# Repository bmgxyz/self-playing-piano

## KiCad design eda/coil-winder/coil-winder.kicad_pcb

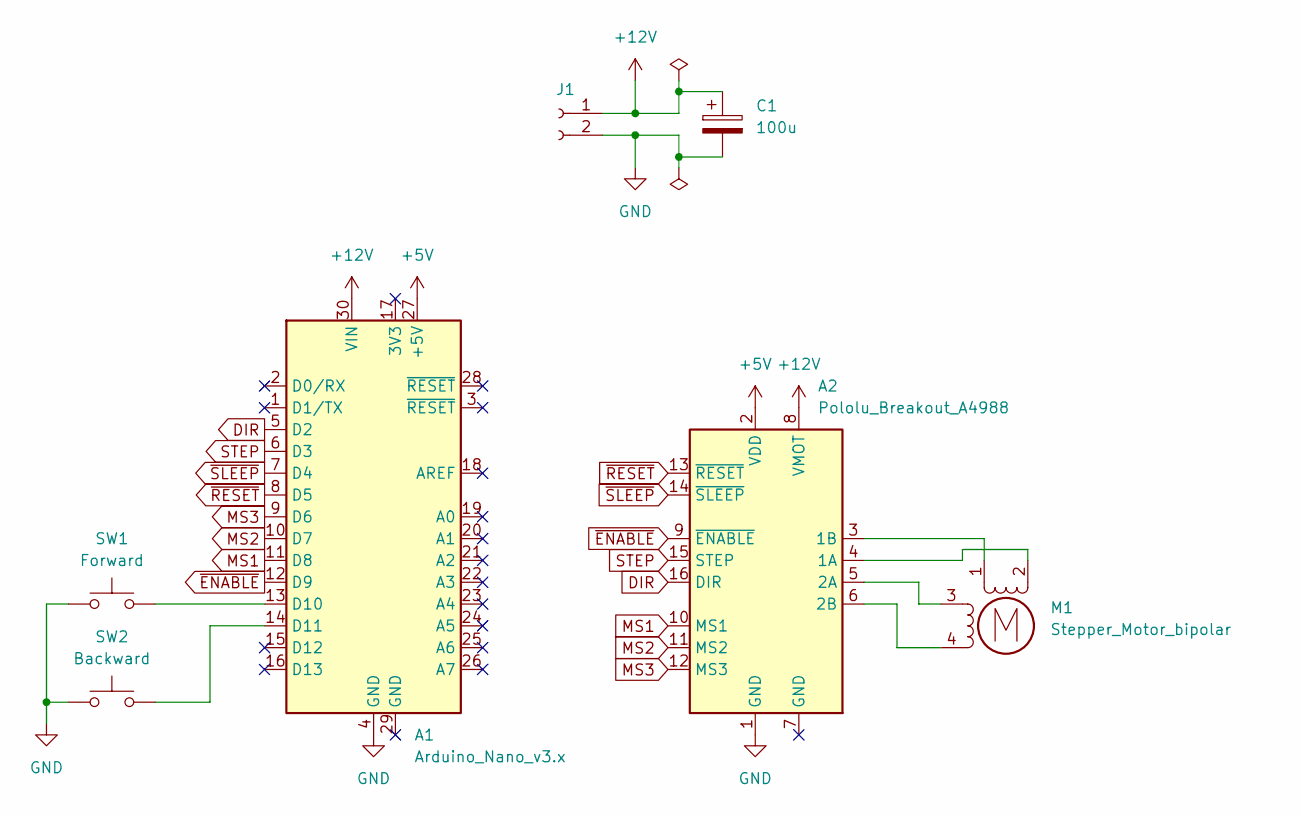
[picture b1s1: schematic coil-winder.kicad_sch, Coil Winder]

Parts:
A1: Arduino_Nano_v3.x; Arduino_Nano
A2: Pololu_Breakout_A4988; Pololu_Breakout-16_15.2x20.3mm
C1: 100u; CP_Radial_D5.0mm_P2.50mm
J1: Conn_01x02_Socket; JST_EH_B2B-EH-A_1x02_P2.50mm_Vertical
M1: Stepper_Motor_bipolar; JST_EH_B2B-EH-A_1x02_P2.50mm_Vertical_Double
SW1: Forward; SW_PUSH_6mm
SW2: Backward; SW_PUSH_6mm

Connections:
+5V: A1.27 (+5V), A2.2 (VDD)
+12V: A1.30 (VIN), A2.8 (VMOT), C1.1, J1.1
DIR: A1.5 (D2), A2.16 (DIR)
GND: A1.4 (GND), A2.1 (GND), C1.2, J1.2, SW1.1, SW2.1
MS1: A1.11 (D8), A2.10 (MS1)
MS2: A1.10 (D7), A2.11 (MS2)
MS3: A1.9 (D6), A2.12 (MS3)
unnamed: A1.13 (D10), SW1.2
unnamed: A1.14 (D11), SW2.2
unnamed: A2.4 (1A), M1.2 (-)
unnamed: A2.3 (1B), M1.1
unnamed: A2.5 (2A), M1.3
unnamed: A2.6 (2B), M1.4
STEP: A1.6 (D3), A2.15 (STEP)
~ENABLE: A1.12 (D9), A2.9 (~ENABLE)
~RESET: A1.8 (D5), A2.13 (~RESET)
~SLEEP: A1.7 (D4), A2.14 (~SLEEP)

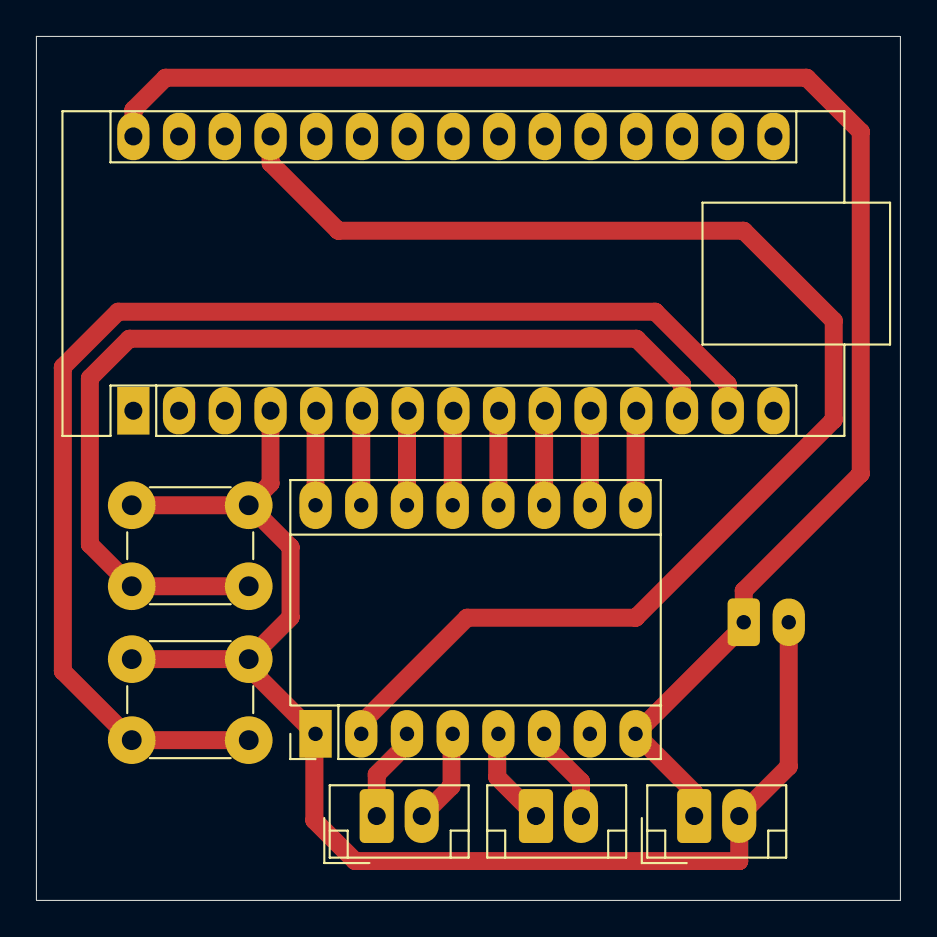
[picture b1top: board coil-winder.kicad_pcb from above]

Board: 2 copper layers, 48.0 x 48.0 mm, 7 parts (0 on the bottom side), 17 nets.

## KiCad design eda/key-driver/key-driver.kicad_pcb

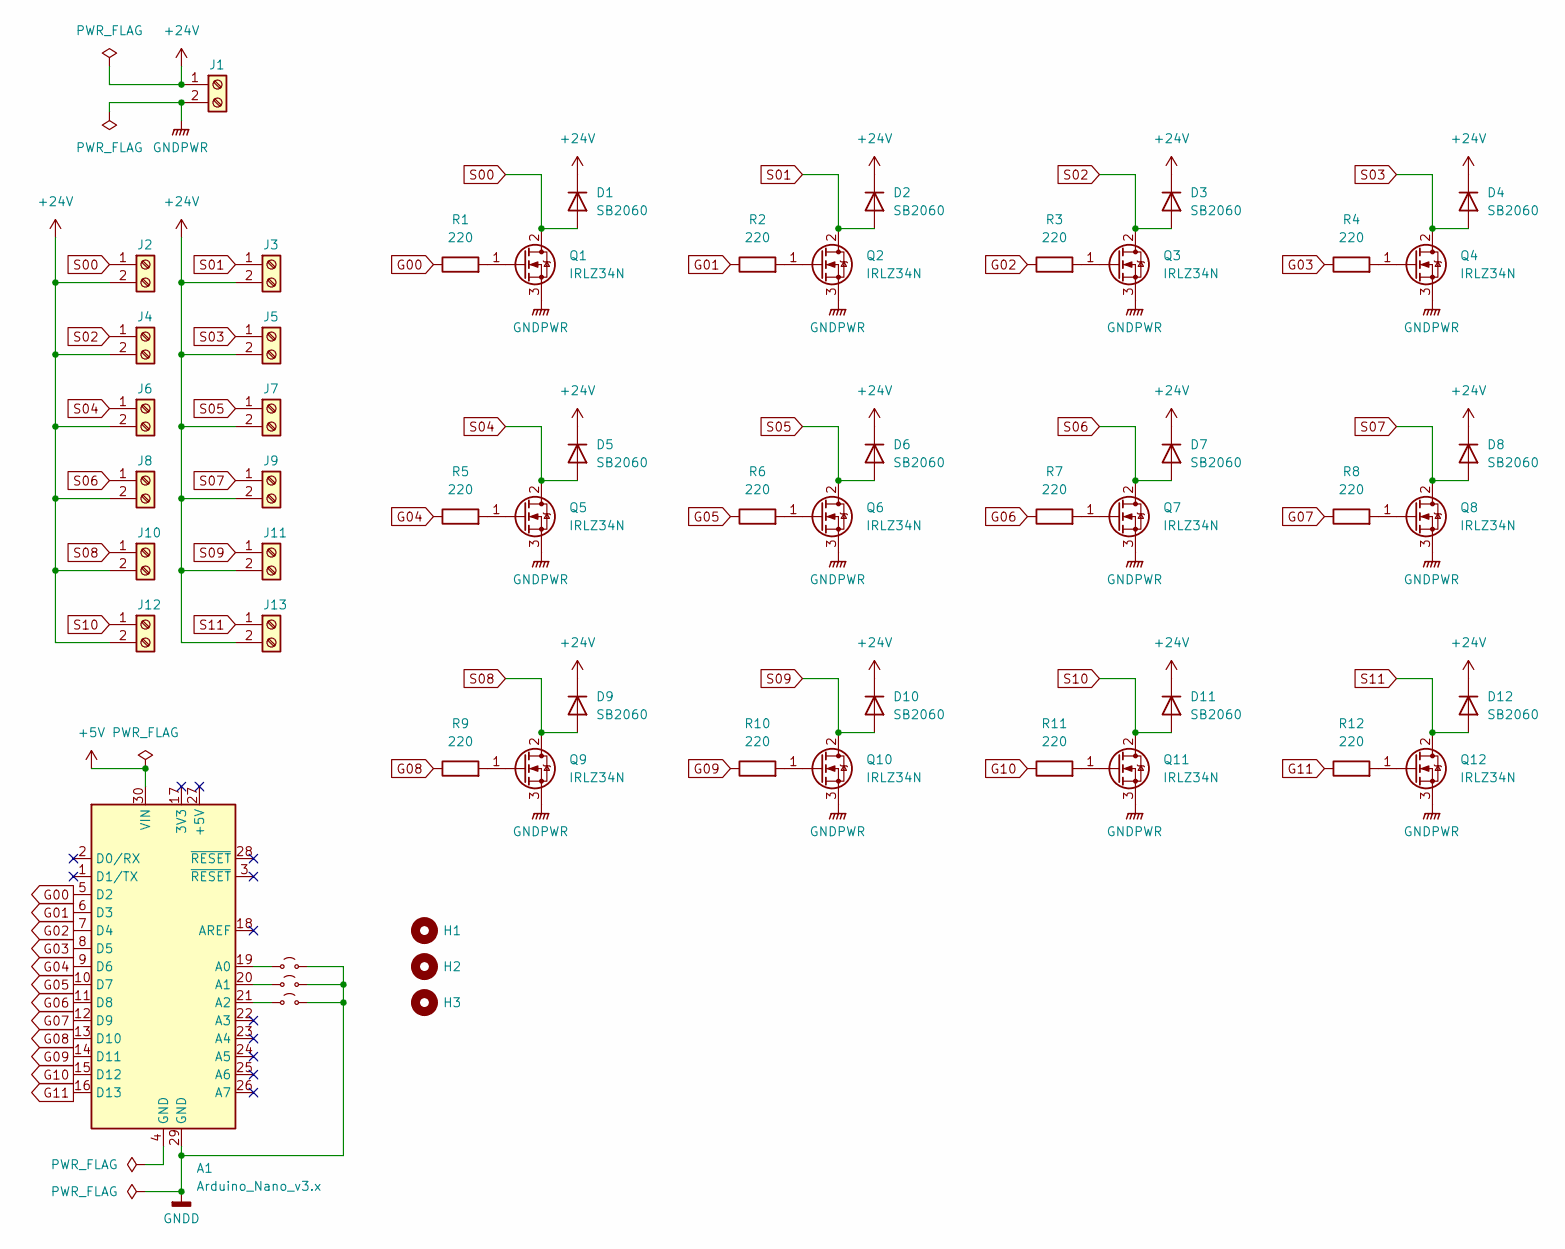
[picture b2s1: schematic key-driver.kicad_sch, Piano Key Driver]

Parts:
A1: Arduino_Nano_v3.x; Arduino_Nano
D1, D2, D3, D4, D5, D6, D7, D8, D9, D10, D11, D12: SB2060; D_DO-201AE_P5.08mm_Vertical_KathodeUp
H1, H2, H3: MountingHole; MountingHole_3.2mm_M3
J1, J2, J3, J4, J5, J6, J7, J8, J9, J10, J11, J12, J13: Screw_Terminal_01x02; JST_EH_B2B-EH-A_1x02_P2.50mm_Vertical
JP1, JP2, JP3: Jumper_2_Small_Open; PinHeader_1x02_P2.54mm_Vertical
Q1, Q2, Q3, Q4, Q5, Q6, Q7, Q8, Q9, Q10, Q11, Q12: IRLZ34N; TO-220-3_Vertical
R1, R2, R3, R4, R5, R6, R7, R8, R9, R10, R11, R12: 220; R_Axial_DIN0204_L3.6mm_D1.6mm_P7.62mm_Horizontal

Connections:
+5V: A1.30 (VIN)
+24V: D1.1 (K), D2.1 (K), D3.1 (K), D4.1 (K), D5.1 (K), D6.1 (K), D7.1 (K), D8.1 (K), D9.1 (K), D10.1 (K), D11.1 (K), D12.1 (K), J1.1, J2.2, J3.2, J4.2, J5.2, J6.2, J7.2, J8.2, J9.2, J10.2, J11.2, J12.2, J13.2
G00: A1.5 (D2), R1.1
G01: A1.6 (D3), R2.1
G02: A1.7 (D4), R3.1
G03: A1.8 (D5), R4.1
G04: A1.9 (D6), R5.1
G05: A1.10 (D7), R6.1
G06: A1.11 (D8), R7.1
G07: A1.12 (D9), R8.1
G08: A1.13 (D10), R9.1
G09: A1.14 (D11), R10.1
G10: A1.15 (D12), R11.1
G11: A1.16 (D13), R12.1
GNDD: A1.29 (GND), JP1.2 (B), JP2.2 (B), JP3.2 (B)
GNDPWR: J1.2, Q1.3 (S), Q2.3 (S), Q3.3 (S), Q4.3 (S), Q5.3 (S), Q6.3 (S), Q7.3 (S), Q8.3 (S), Q9.3 (S), Q10.3 (S), Q11.3 (S), Q12.3 (S)
unnamed: A1.19 (A0), JP1.1 (A)
unnamed: A1.20 (A1), JP2.1 (A)
unnamed: A1.21 (A2), JP3.1 (A)
unnamed: Q1.1 (G), R1.2
unnamed: Q2.1 (G), R2.2
unnamed: Q3.1 (G), R3.2
unnamed: Q4.1 (G), R4.2
unnamed: Q5.1 (G), R5.2
unnamed: Q6.1 (G), R6.2
unnamed: Q7.1 (G), R7.2
unnamed: Q8.1 (G), R8.2
unnamed: Q9.1 (G), R9.2
unnamed: Q10.1 (G), R10.2
unnamed: Q11.1 (G), R11.2
unnamed: Q12.1 (G), R12.2
S00: D1.2 (A), J2.1, Q1.2 (D)
S01: D2.2 (A), J3.1, Q2.2 (D)
S02: D3.2 (A), J4.1, Q3.2 (D)
S03: D4.2 (A), J5.1, Q4.2 (D)
S04: D5.2 (A), J6.1, Q5.2 (D)
S05: D6.2 (A), J7.1, Q6.2 (D)
S06: D7.2 (A), J8.1, Q7.2 (D)
S07: D8.2 (A), J9.1, Q8.2 (D)
S08: D9.2 (A), J10.1, Q9.2 (D)
S09: D10.2 (A), J11.1, Q10.2 (D)
S10: D11.2 (A), J12.1, Q11.2 (D)
S11: D12.2 (A), J13.1, Q12.2 (D)

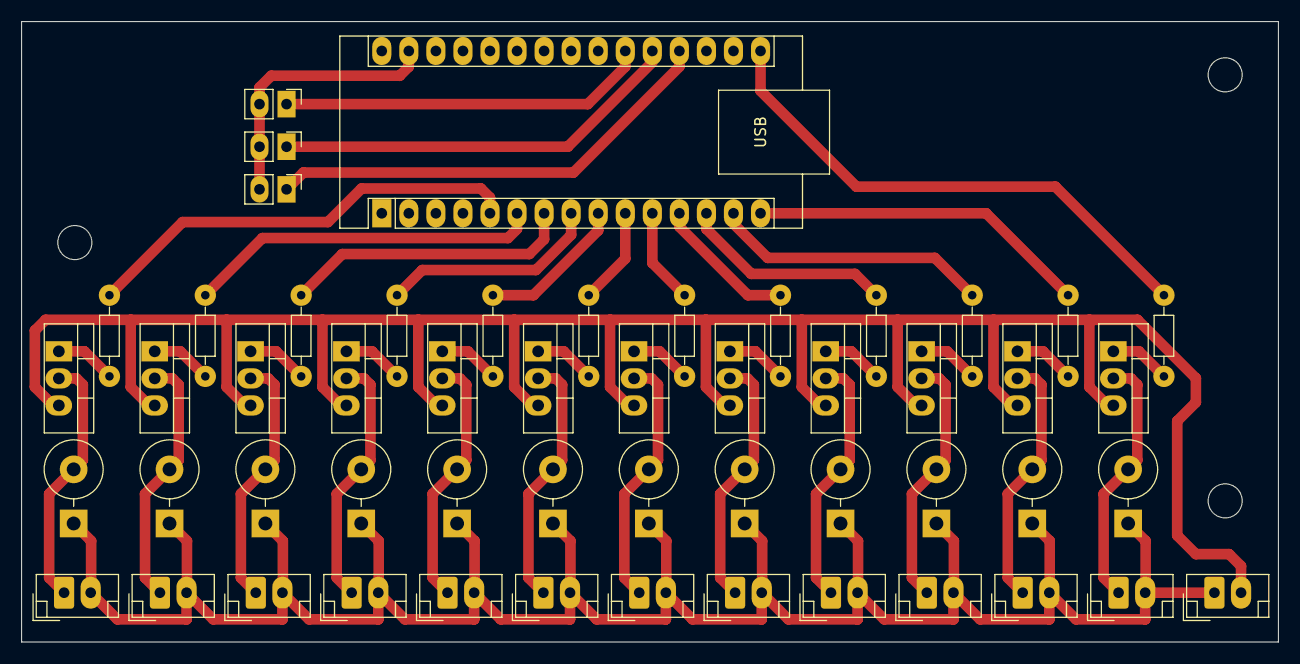
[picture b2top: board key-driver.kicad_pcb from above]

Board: 2 copper layers, 118.0 x 58.2 mm, 56 parts (0 on the bottom side), 42 nets.

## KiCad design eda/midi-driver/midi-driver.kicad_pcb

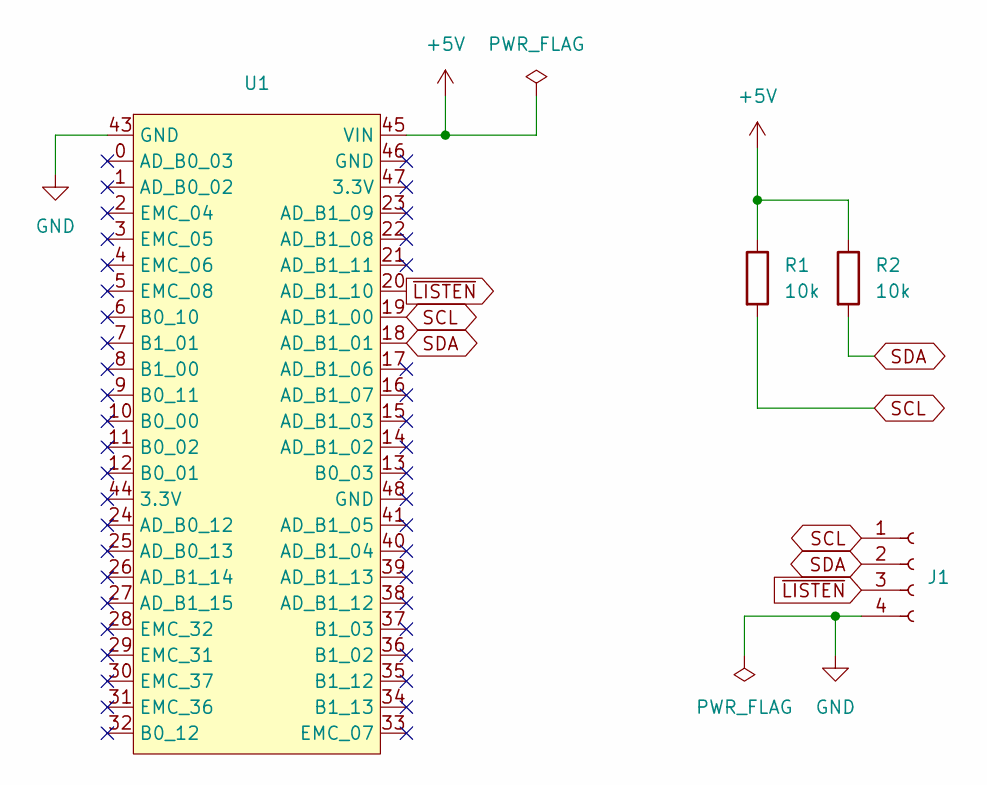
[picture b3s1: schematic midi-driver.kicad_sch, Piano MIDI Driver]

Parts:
J1: Conn_01x04_Socket; PinSocket_1x04_P2.54mm_Vertical
R1, R2: 10k; R_Axial_DIN0204_L3.6mm_D1.6mm_P7.62mm_Horizontal
U1: Teensy41

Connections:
+5V: R1.1, R2.1, U1.45 (VIN)
GND: J1.4, U1.43 (GND)
SCL: J1.1, R1.2, U1.19 (AD_B1_00)
SDA: J1.2, R2.2, U1.18 (AD_B1_01)
~LISTEN: J1.3, U1.20 (AD_B1_10)

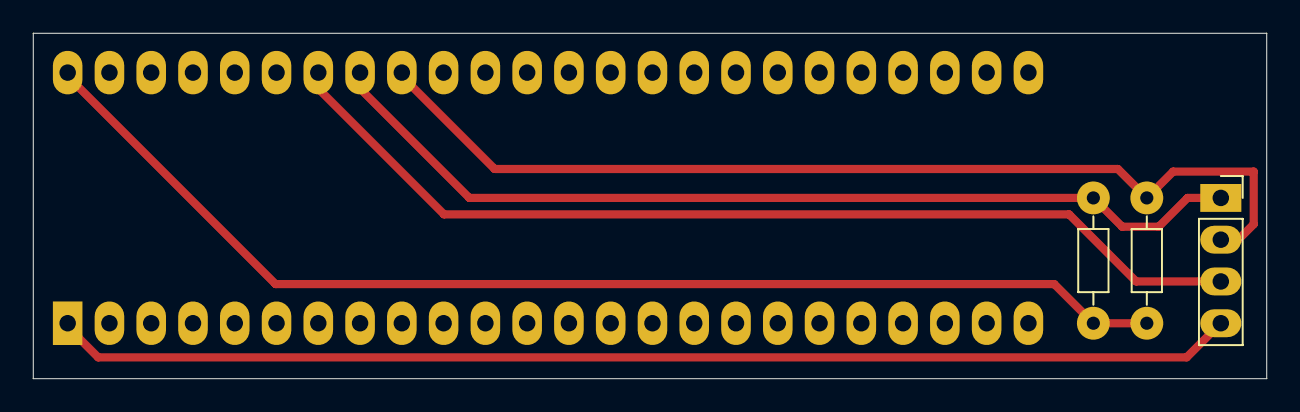
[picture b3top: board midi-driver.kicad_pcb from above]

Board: 2 copper layers, 75.0 x 21.0 mm, 4 parts (0 on the bottom side), 5 nets.

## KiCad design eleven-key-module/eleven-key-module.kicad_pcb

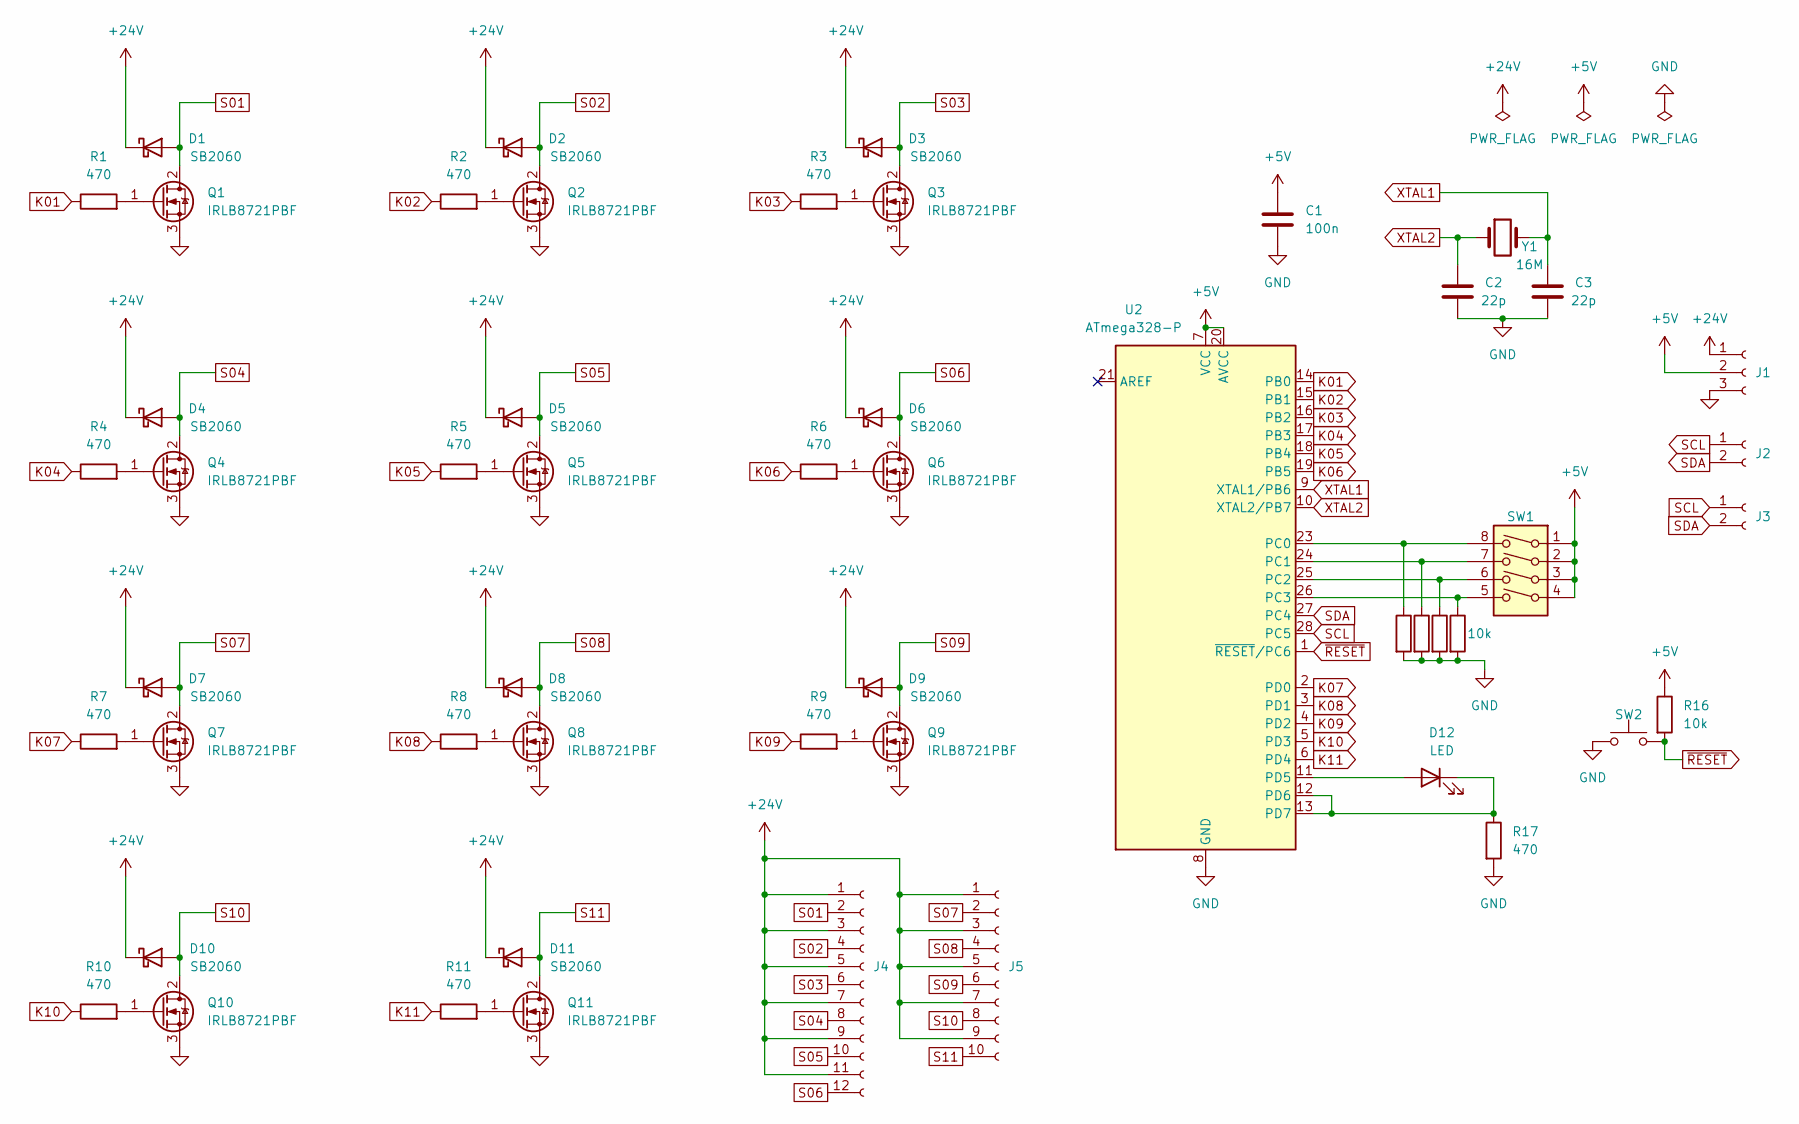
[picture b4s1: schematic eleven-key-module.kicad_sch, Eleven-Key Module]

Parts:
C1: 100n; C_Rect_L4.6mm_W3.8mm_P2.50mm_MKS02_FKP02
C2, C3: 22p; C_Rect_L4.0mm_W2.5mm_P2.50mm
D1, D2, D3, D4, D5, D6, D7, D8, D9, D10, D11: SB2060; D_DO-201AD_P15.24mm_Horizontal
D12: LED; LED_D5.0mm
J1: Conn_01x03_Socket; TerminalBlock_Xinya_XY308-2.54-3P_1x03_P2.54mm_Horizontal
J2, J3: Conn_01x02_Female; PinHeader_1x02_P2.54mm_Vertical
J4: Conn_01x12_Socket; TerminalBlock_Xinya_XY308-2.54-12P_1x12_P2.54mm_Horizontal
J5: Conn_01x10_Socket; TerminalBlock_Xinya_XY308-2.54-10P_1x10_P2.54mm_Horizontal
Q1, Q2, Q3, Q4, Q5, Q6, Q7, Q8, Q9, Q10, Q11: IRLB8721PBF; TO-220-3_Vertical
R1, R2, R3, R4, R5, R6, R7, R8, R9, R10, R11, R17: 470; R_Axial_DIN0204_L3.6mm_D1.6mm_P7.62mm_Horizontal
R12, R13, R14, R15, R16: 10k; R_Axial_DIN0204_L3.6mm_D1.6mm_P7.62mm_Horizontal
SW1: SW_DIP_x04; DIP-8_W7.62mm
SW2: SW_Push; SW_PUSH_6mm
U2: ATmega328-P; DIP-28_W7.62mm
Y1: 16M; Crystal_HC49-U_Vertical

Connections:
+5V: C1.1, J1.2, R16.1, SW1.1, SW1.2, SW1.3, SW1.4, U2.7 (VCC), U2.20 (AVCC)
+24V: D1.1 (K), D2.1 (K), D3.1 (K), D4.1 (K), D5.1 (K), D6.1 (K), D7.1 (K), D8.1 (K), D9.1 (K), D10.1 (K), D11.1 (K), J1.1, J4.1, J4.3, J4.5, J4.7, J4.9, J4.11, J5.1, J5.3, J5.5, J5.7, J5.9
GND: C1.2, C2.1, C3.1, J1.3, Q1.3 (S), Q2.3 (S), Q3.3 (S), Q4.3 (S), Q5.3 (S), Q6.3 (S), Q7.3 (S), Q8.3 (S), Q9.3 (S), Q10.3 (S), Q11.3 (S), R12.2, R13.2, R14.2, R15.2, R17.2, SW2.1, U2.8 (GND), U2.22 (GND)
K01: R1.1, U2.14 (PB0)
K02: R2.1, U2.15 (PB1)
K03: R3.1, U2.16 (PB2)
K04: R4.1, U2.17 (PB3)
K05: R5.1, U2.18 (PB4)
K06: R6.1, U2.19 (PB5)
K07: R7.1, U2.2 (PD0)
K08: R8.1, U2.3 (PD1)
K09: R9.1, U2.4 (PD2)
K10: R10.1, U2.5 (PD3)
K11: R11.1, U2.6 (PD4)
unnamed: D12.2 (A), U2.11 (PD5)
unnamed: D12.1 (K), R17.1, U2.12 (PD6), U2.13 (PD7)
unnamed: Q1.1 (G), R1.2
unnamed: Q2.1 (G), R2.2
unnamed: Q3.1 (G), R3.2
unnamed: Q4.1 (G), R4.2
unnamed: Q5.1 (G), R5.2
unnamed: Q6.1 (G), R6.2
unnamed: Q7.1 (G), R7.2
unnamed: Q8.1 (G), R8.2
unnamed: Q9.1 (G), R9.2
unnamed: Q10.1 (G), R10.2
unnamed: Q11.1 (G), R11.2
unnamed: R12.1, SW1.8, U2.23 (PC0)
unnamed: R13.1, SW1.7, U2.24 (PC1)
unnamed: R14.1, SW1.6, U2.25 (PC2)
unnamed: R15.1, SW1.5, U2.26 (PC3)
S01: D1.2 (A), J4.2, Q1.2 (D)
S02: D2.2 (A), J4.4, Q2.2 (D)
S03: D3.2 (A), J4.6, Q3.2 (D)
S04: D4.2 (A), J4.8, Q4.2 (D)
S05: D5.2 (A), J4.10, Q5.2 (D)
S06: D6.2 (A), J4.12, Q6.2 (D)
S07: D7.2 (A), J5.2, Q7.2 (D)
S08: D8.2 (A), J5.4, Q8.2 (D)
S09: D9.2 (A), J5.6, Q9.2 (D)
S10: D10.2 (A), J5.8, Q10.2 (D)
S11: D11.2 (A), J5.10, Q11.2 (D)
SCL: J2.1, J3.1, U2.28 (PC5)
SDA: J2.2, J3.2, U2.27 (PC4)
XTAL1: C3.2, U2.9 (XTAL1/PB6), Y1.2
XTAL2: C2.2, U2.10 (XTAL2/PB7), Y1.1
~RESET: R16.2, SW2.2, U2.1 (~RESET/PC6)

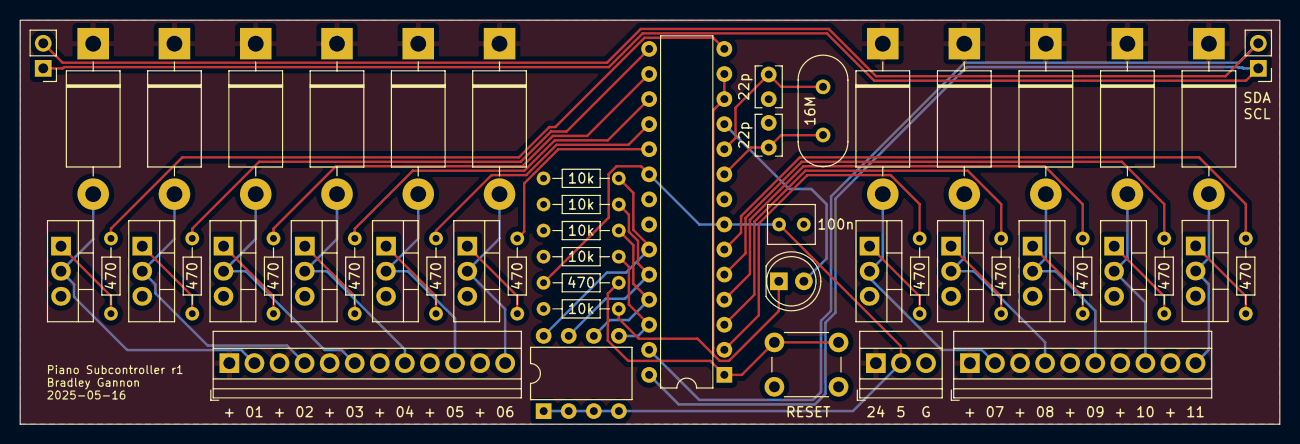
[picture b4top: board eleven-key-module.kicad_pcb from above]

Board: 2 copper layers, 127.6 x 40.9 mm, 52 parts (0 on the bottom side), 47 nets.

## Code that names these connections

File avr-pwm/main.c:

#include <avr/io.h>
#include <avr/interrupt.h>
#include <stdbool.h>

#define TWI_ACK_NEXT  { TWCR = (1 << TWINT) | (1 << TWEN) | (1 << TWEA) | (1 << TWIE); }
#define TWI_NACK_NEXT { TWCR = (1 << TWINT) | (1 << TWEN) | (1 << TWIE); }

extern void pwm(uint8_t *table_b, uint8_t *table_d);

// libc zeros these arrays automatically
static uint8_t table_b[127];
static uint8_t table_d[127];

enum state {
    idle, first, second, third
};

static volatile enum state s = idle;
static volatile uint16_t message = 0;
static volatile uint8_t key_idx = 0;
static volatile uint8_t key_vel = 0;

const uint8_t TWI_ADDR_PREFIX = 0x50;

void update_pwm(uint8_t key_idx, uint8_t key_vel) {
    uint8_t table_idx = key_idx < 6 ? key_idx : key_idx - 6;
    uint8_t *table_to_update = key_idx < 6 ? table_b : table_d;
    for (int i = 0; i < 127; i++) {
        if (i < key_vel) {
            // set bit
            table_to_update[i] |= 1 << table_idx;
        } else {
            // clear bit
            table_to_update[i] &= ~(1 << table_idx);
        }
    }
}

bool valid_checksum(uint16_t message) {
    return __builtin_popcount(message) % 6 == 0;
}

ISR(TWI_vect) {
    // quoted comments for each case come from Table 21-5 in the datasheet
    switch (TWSR & 0xf8) {
        // "Own SLA+W has been received; ACK has been returned"
        case 0x60:
            message = 0;
            key_idx = 0;
            key_vel = 0;
            s = first;
            TWI_ACK_NEXT
            break;
        // "Previously addressed with own SLA+W; data has been received; ACK has been returned"
        case 0x80:
            switch (s) {
                case first:
                    message = ((uint16_t)TWDR) << 8;
                    s = second;
                    TWI_ACK_NEXT
                    break;
                case second:
                    message |= ((uint16_t)TWDR);
                    s = third;
                    key_idx = (uint8_t)(message >> 12);
                    key_vel = (uint8_t)((message >> 5) % (1 << 7));
                    if (key_idx < 11 && valid_checksum(message)) {
                        update_pwm(key_idx, key_vel);
                        TWI_ACK_NEXT
                    } else {
                        TWI_NACK_NEXT
                    }
                    break;
                default:
                    s = idle;
                    TWI_ACK_NEXT
                    break;
            }
            break;
        default:
            message = 0;
            key_idx = 0;
            key_vel = 0;
            s = idle;
            TWI_ACK_NEXT
            break;
    }
}

int main(void) {
    DDRB = 0b00111111; // PB0 through PB5
    DDRD = 0b00111111; // PD0 through PD4, plus PD5 for status LED

    // I2C address is equal to the prefix together with the low nibble of PINC
    // shifted left by one to avoid TWGCE in TWAR
    TWAR = (TWI_ADDR_PREFIX | (PINC & 0b111)) << 1;

    // configure I2C for slave receiver mode with interrupts
    TWCR = (1 << TWEA) | (1 << TWEN) | (1 << TWIE);
    TWI_ACK_NEXT

    // enable global interrupts
    sei();

    while (1) {
        if (PINC & (1 << PC3)) {
            PORTD |= 1 << PD5;
            pwm(table_b, table_d);
            PORTD &= ~(1 << PD5);
        }
    }
}

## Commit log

2024-04-02 Add solenoid actuator model
2024-08-09 Tweak solenoid model and move to subdir
2024-08-09 Add initial controller code
2024-08-09 Add initial FPGA code
2024-08-09 Add existing CadQuery models
2024-08-10 Refactor CAD models
2024-09-01 Make various CAD improvements and tweaks
2024-09-01 Add code for generating MIDI test files
2024-09-01 Add schematic and PCB for eleven key module
2024-09-01 Add PWM scaling, add transition diagram, improve FSM, add Makefile
2024-09-02 Fix some controller bugs after testing
2024-09-04 Set initial FPGA outputs to logic high
2024-09-04 Decrease FPGA clock frequency to give ~20 kHz PWM output
2024-09-06 Make initial changes to switch to AVR PWM
2024-09-06 Add code for AVR PWM
2024-09-06 Remove code for FPGA PWM
2024-09-07 Update controller to support all keys
2024-10-15 Switch schematic to Atmega328P
2024-10-15 Add serial logging, update PWM values, some tweaks
2024-10-15 Tweak a few values to improve fit, add key platform window
2024-10-15 Add script to estimate solenoid wire length
2025-04-30 Switch to I2C on subcontroller
2025-05-01 Switch to I2C on main controller
2025-05-01 Bump deps, continue I2C switch, and minor reformatting
2025-05-01 Replace global logger with version that's passed by reference as needed
2025-05-02 Appease clippy
2025-05-03 Fix new logging system
2025-05-06 Fix I2C and PWM on subcontroller
2025-05-06 Refactor state management on main controller
2025-05-06 Break main.rs into several modules
2025-05-06 Fix lingering controller communication issues and test end-to-end (MIDI to PWM)
2025-05-12 Fix I2C for standalone Atmega328P
2025-05-13 Fix logic bug in subcontroller address
2025-05-16 Update KiCad version and convert schematic to I2C
2025-05-16 Further update schematic and create PCB
2025-05-31 Refactor key platform and generally improve CAD code
2025-05-31 Remove steel support and solenoid winder CAD models
2025-05-31 Slightly tweak parameters related to platform height
2025-06-10 Refactor controller protocol with checksum, use ISR on subcontroller
2025-06-15 Add control signal to stop PWM during I2C transactions
2025-06-17 Fix checksum on main controller
2025-07-04 Switch main controller to enhanced shift register approach
2025-07-04 Remove AVR PWM
2025-07-06 Add hold PWM signal generation
2025-07-17 Migrate to RTIC and handle USB with interrupt
2025-08-09 Reorg EDA code, modify key driver to use Arduino Nano
2025-08-09 Collect all firmware into one dir, add key driver code based on Arduino Nano and common library code
2025-08-09 Remove old eleven-key-module KiCad project
2025-08-09 Move .gitignore for EDA up one level and add blank KiCad project for MIDI driver
2025-08-15 Improve key driver circuit (r3)
2025-08-15 Add MIDI driver circuit (r1)
2025-08-15 Remove old MIDI driver firmware, which I added by mistake
2025-08-15 Remove key-driver.hex, which I added by mistake
2025-08-16 Fix some firmware bugs
2025-08-21 Modify key driver code to use a schedule and read it from serial
2025-08-21 Add host-side bothoven binary to control key drivers
2025-08-21 Move transition diagram into bothoven
2025-08-21 Remove MIDI driver
2025-08-21 Add Makefile to bothoven for transition diagram
2025-08-24 Add host-side MIDI input and processing
2025-08-25 Make the default PWM schedule set all key pins low, and other improvements
2025-08-25 Fix key driver pin assignment error from testing
2025-10-18 Add end support CAD model
2025-10-22 Add end support spacer, reorg a bit
2025-10-22 Switch to uv
2025-10-22 Migrate key platform to new wood rail approach and remove old code for standalone platform
2025-11-17 Modify key support CAD code to use new key arrangement
2025-11-17 Modify key driver schematic and PCB to use new key arrangement, JST connectors, and wider traces
2025-11-17 Modify key driver firmware to use new key arrangement
2025-11-20 Improve performance of key driver schedule code
2025-12-26 Add coil winder
2026-02-15 Modify plunger design to load from above instead of below the solenoids
2026-02-23 Make host code handle multiple key drivers and bump some deps
2026-03-26 Interpret note on MIDI messages with zero velocity as note off
